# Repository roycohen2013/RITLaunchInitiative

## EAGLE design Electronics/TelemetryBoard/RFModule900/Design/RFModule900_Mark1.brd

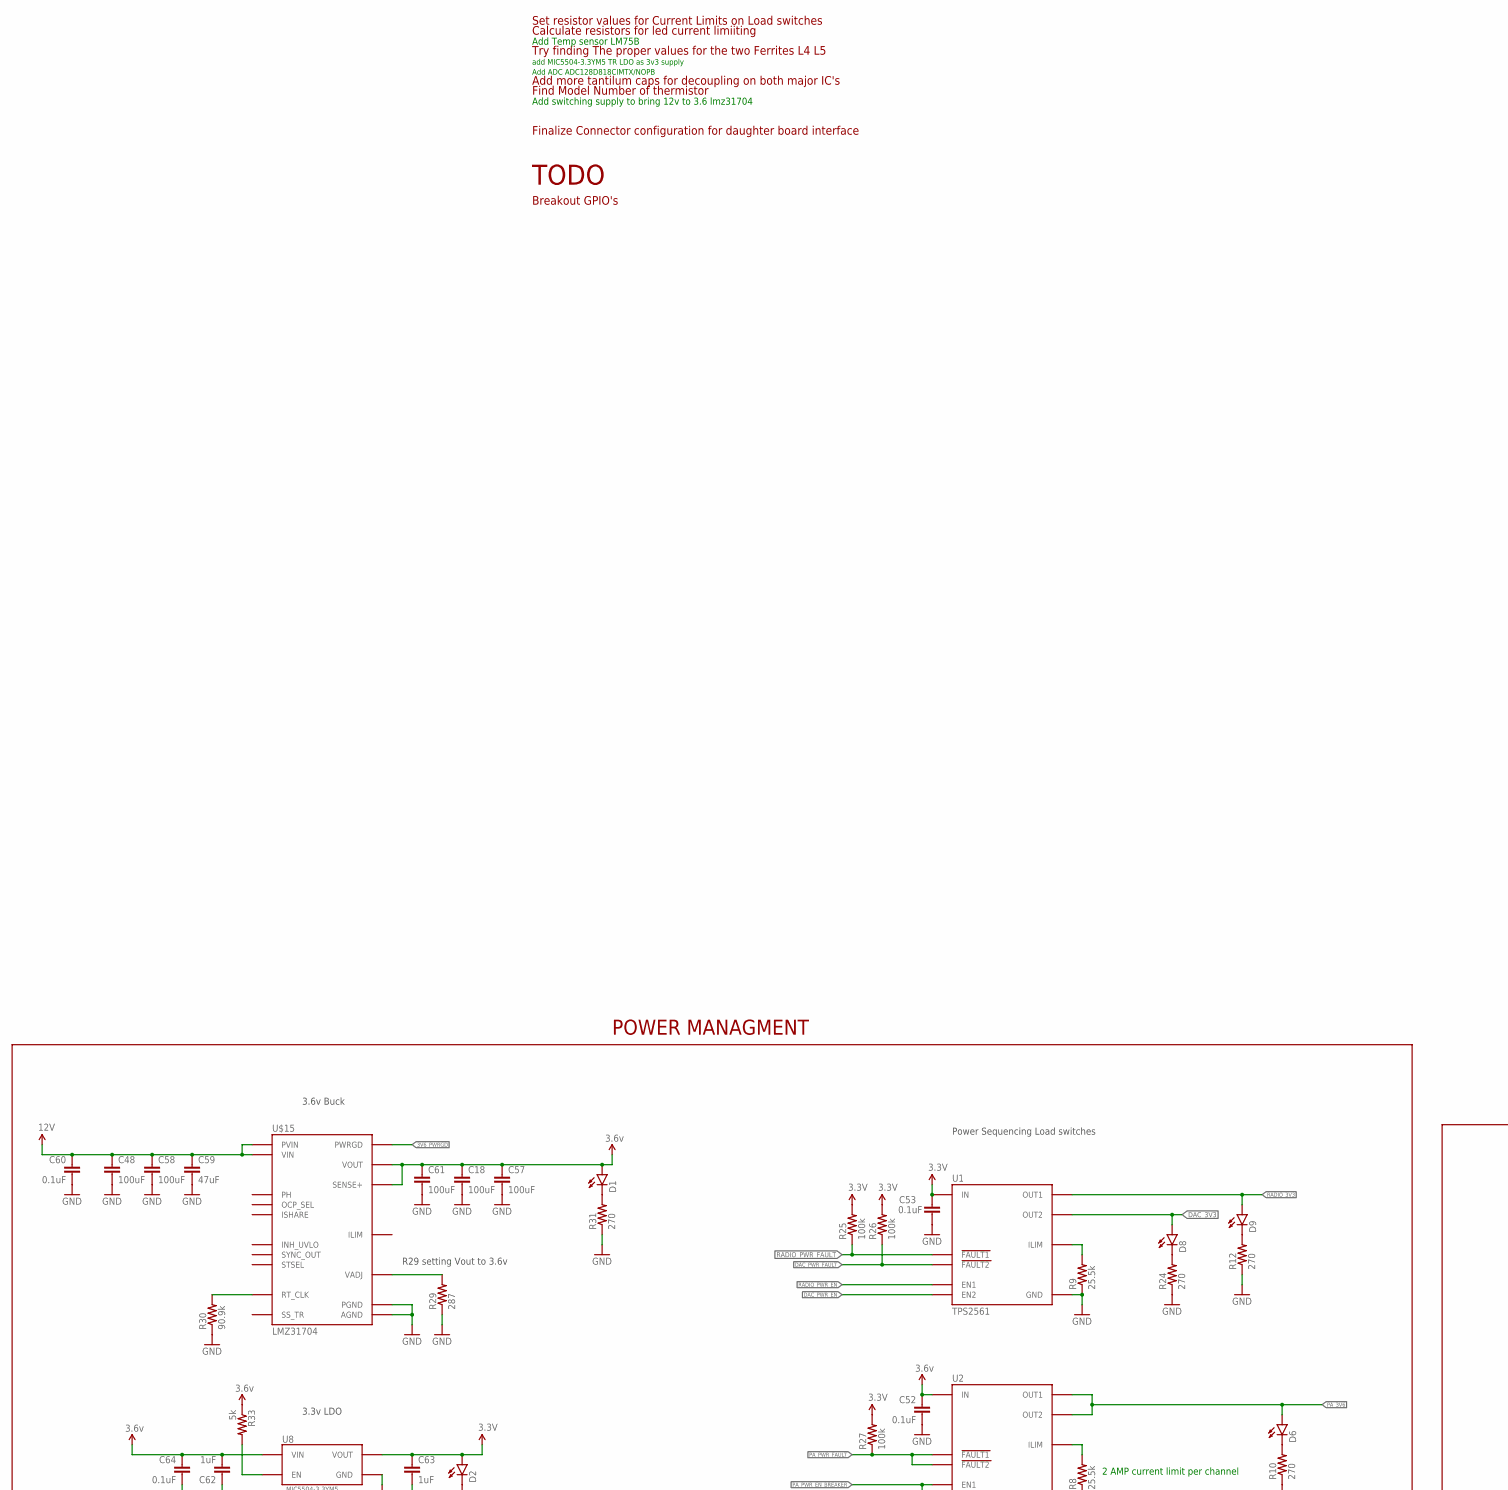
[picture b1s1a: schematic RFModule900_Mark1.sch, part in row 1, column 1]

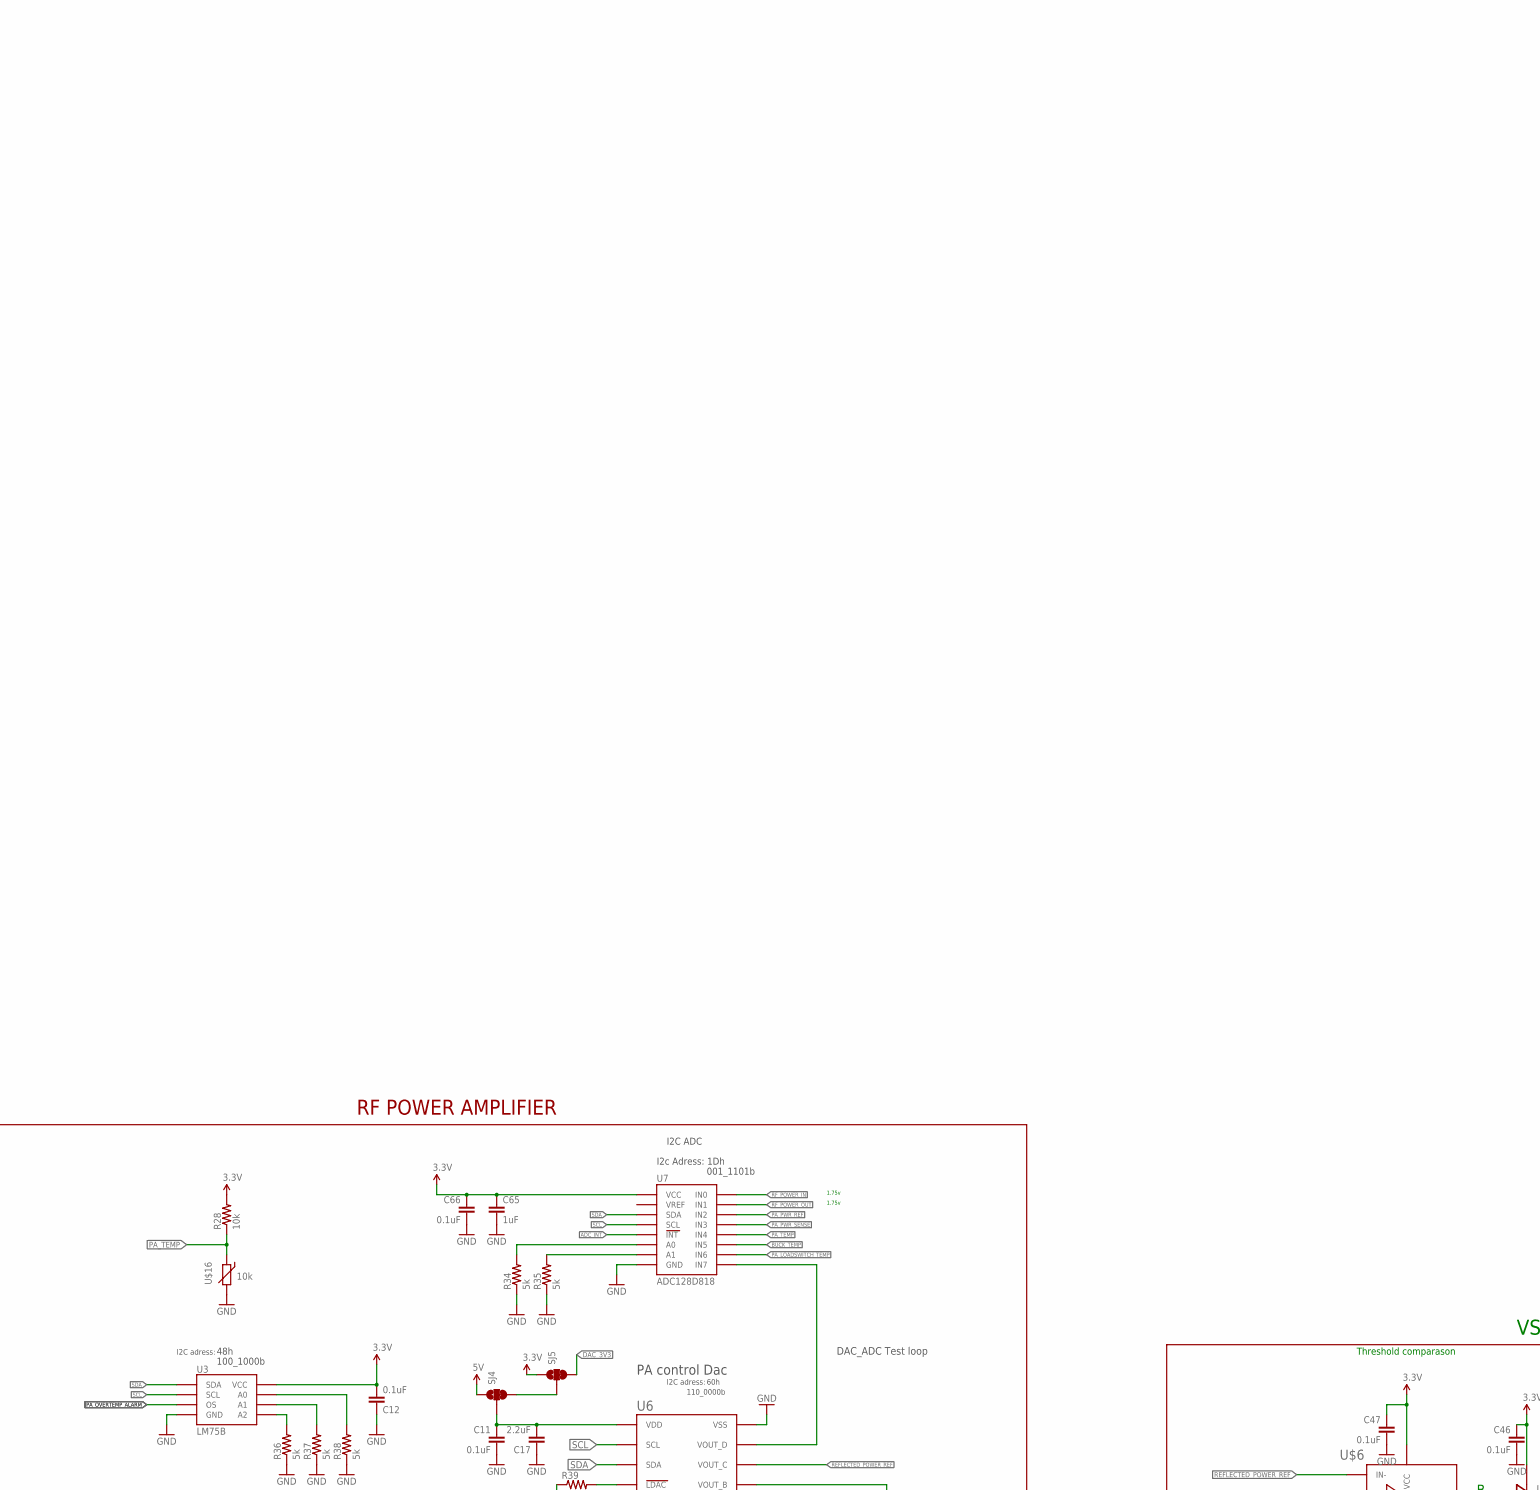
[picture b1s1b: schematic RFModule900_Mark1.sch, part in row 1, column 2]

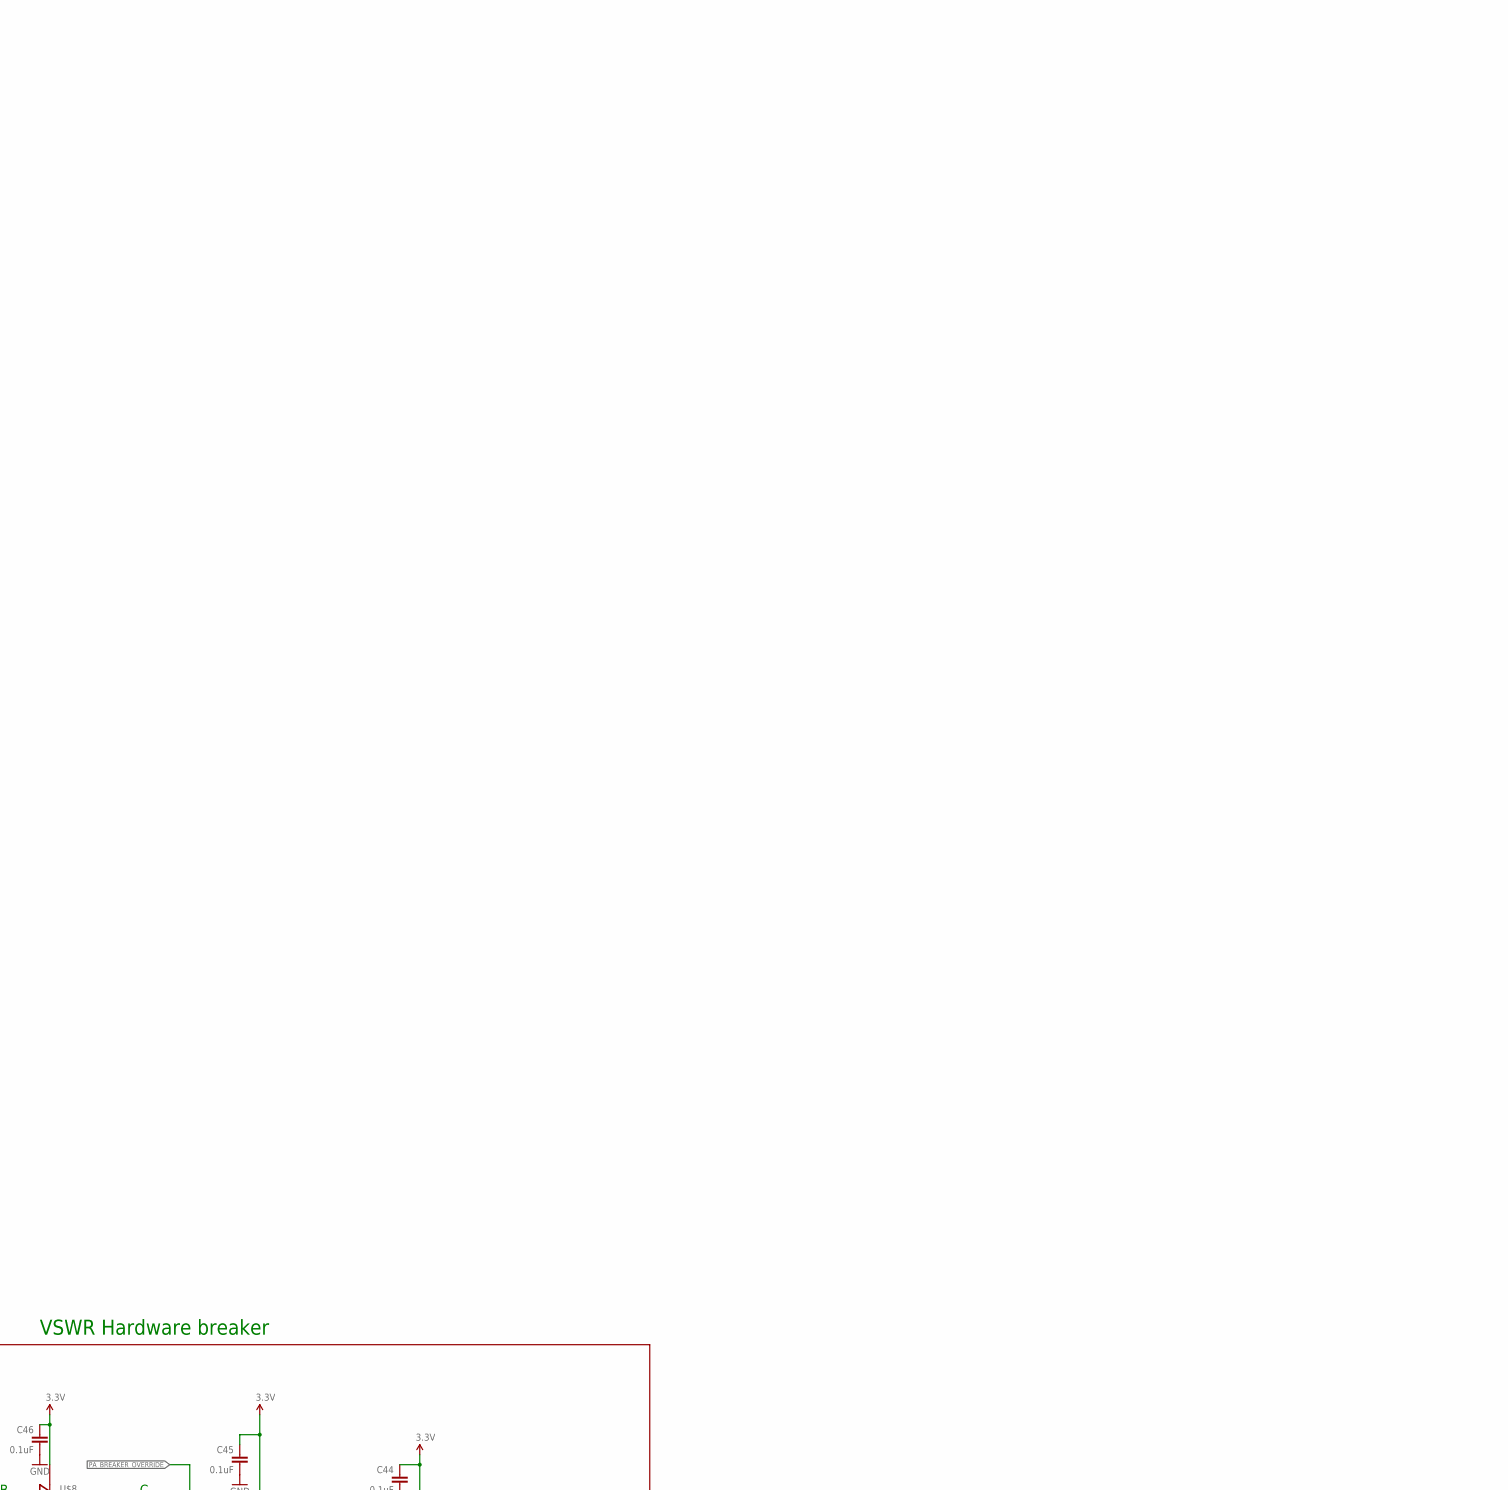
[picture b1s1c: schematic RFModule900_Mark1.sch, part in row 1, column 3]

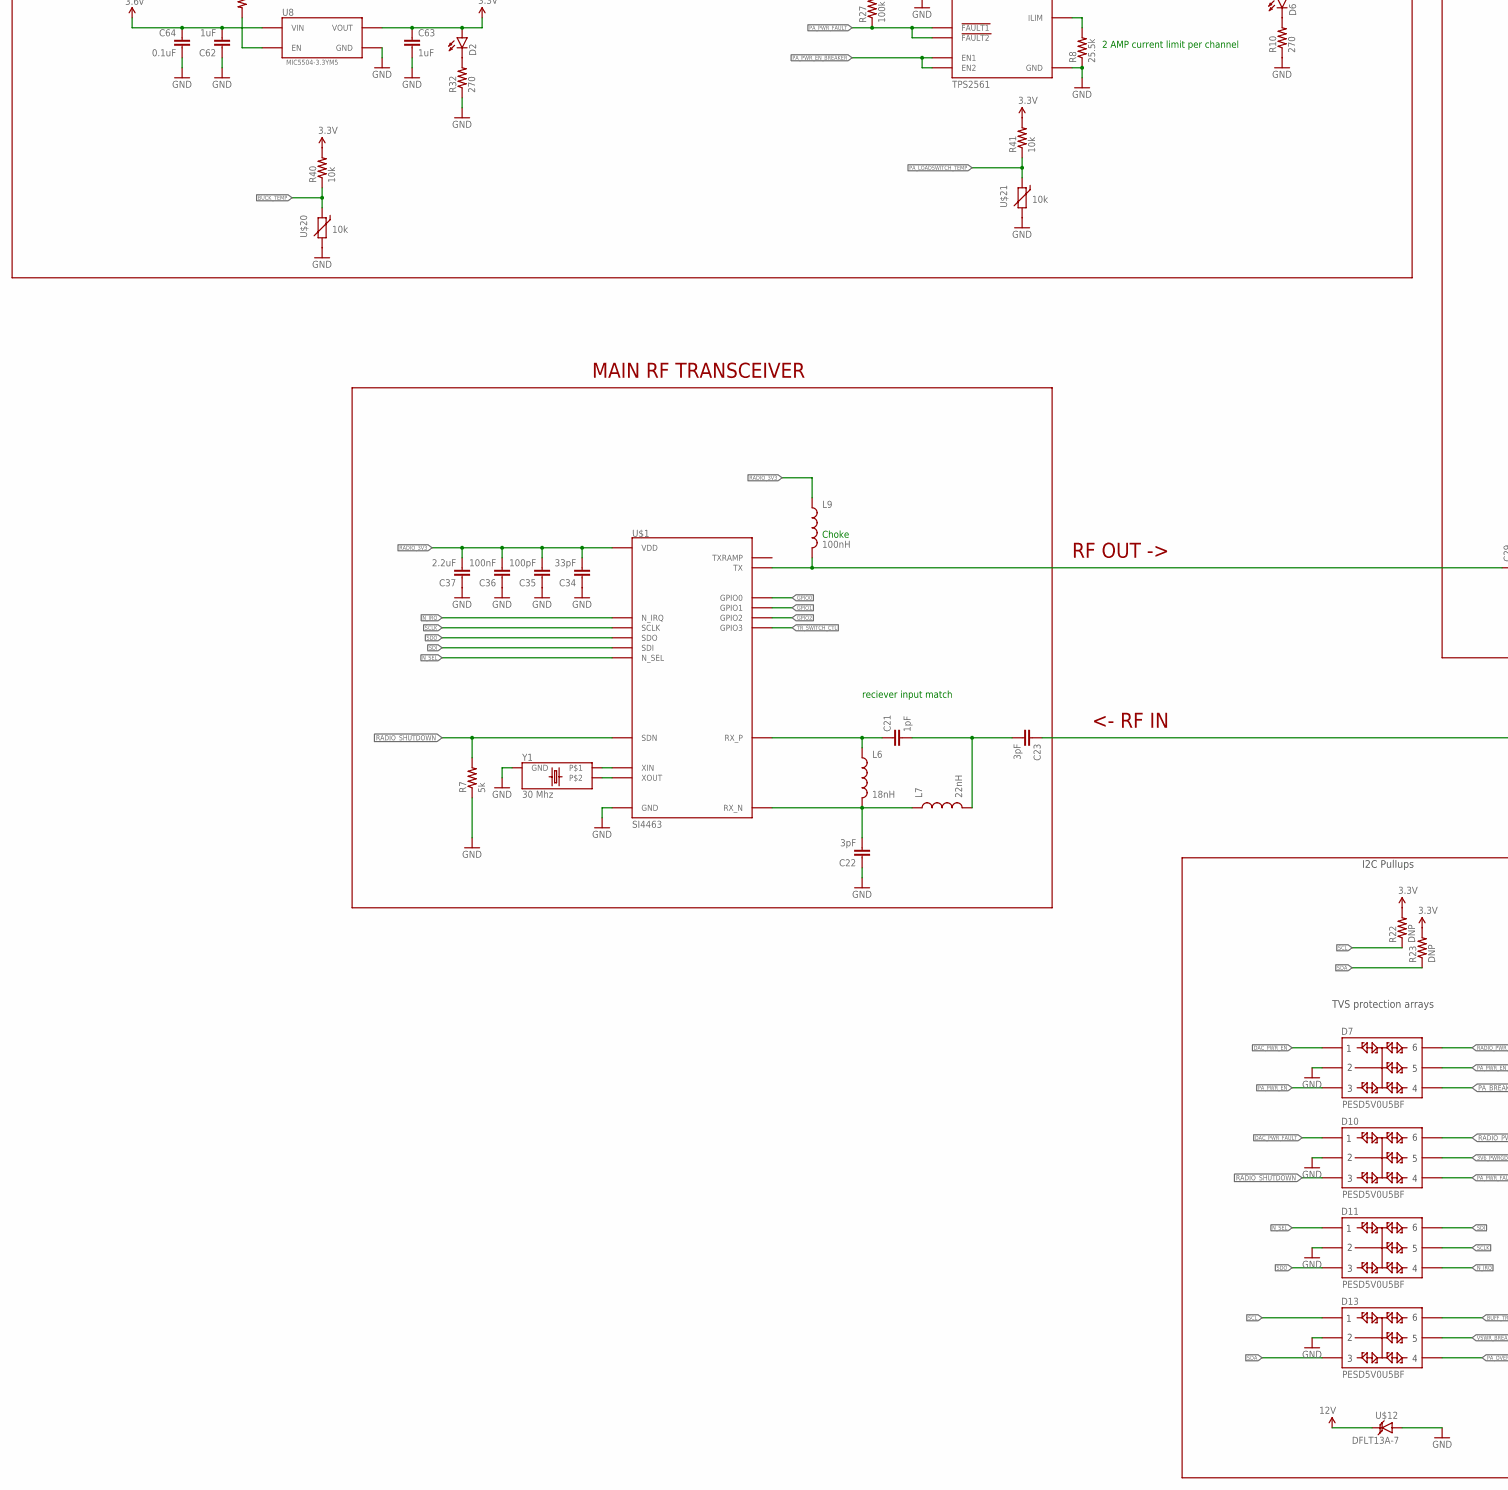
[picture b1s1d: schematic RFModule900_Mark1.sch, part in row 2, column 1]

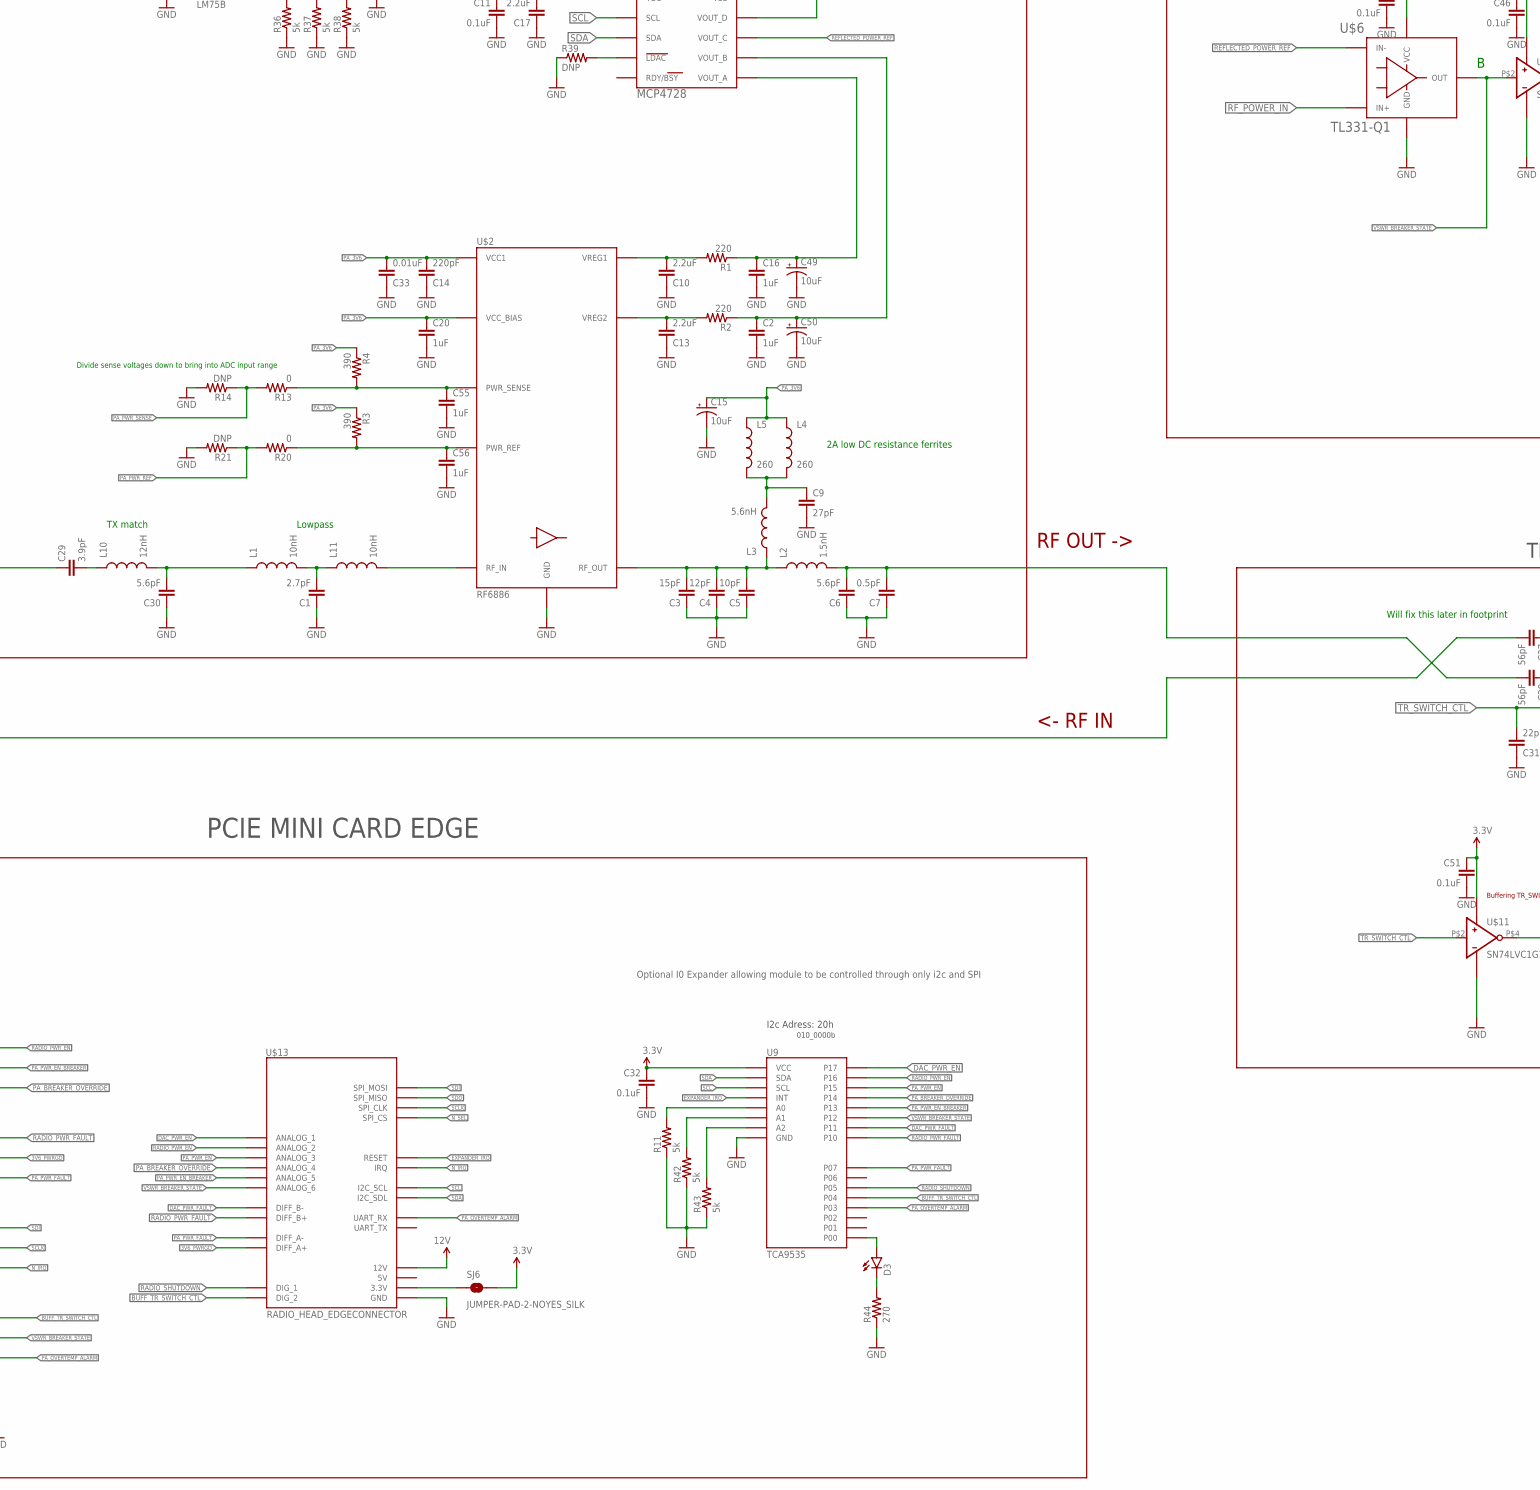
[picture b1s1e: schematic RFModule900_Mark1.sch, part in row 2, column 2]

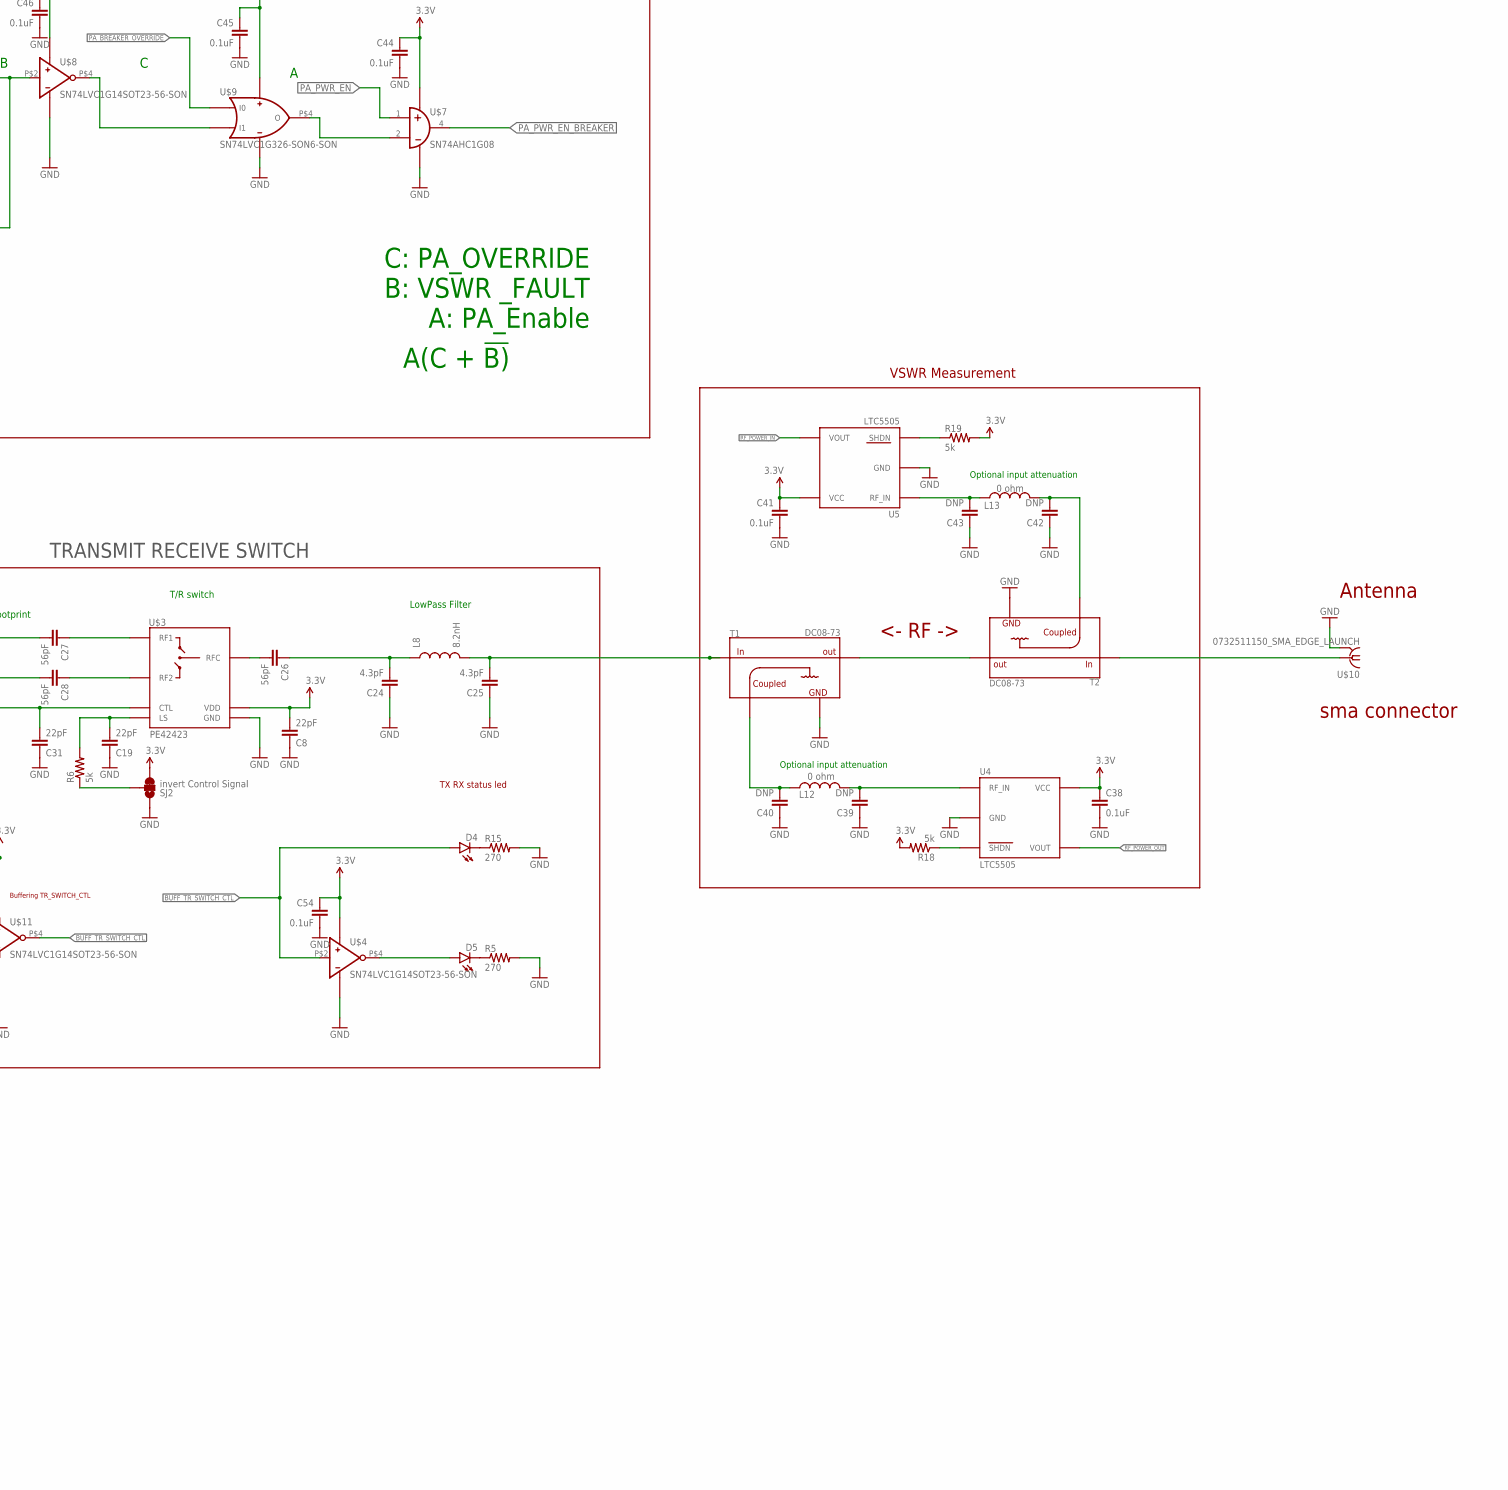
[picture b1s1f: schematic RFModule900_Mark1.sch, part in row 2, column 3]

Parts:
C1: 2.7pF; 0402-CAP
C2, C16: 1uF; 0402-CAP; MPN JMK105BJ225MVHF; DIGI 587-1453-1-ND
C3: 15pF; 0402-CAP; MPN 500R07S150JV4TD; DIGI 712-1261-1-ND
C4: 12pF; 0402-CAP; MPN 500R07S120JV4TD; DIGI 712-1257-1-ND
C5: 10pF; 0402-CAP; MPN 500R07S100JV4TD; DIGI 712-1253-1-ND
C6: 5.6pF; 0402-CAP; MPN 500R07S5R6BV4; MOUSER 609-500R07S5R6BV4T
C7: 0.5pF; 0402-CAP; MPN 500R07S0R5BV4TD; DIGI 712-1162-1-ND
C8, C19, C31: 22pF; 0402-CAP
C9: 27pF; 0402-CAP; DIGI 712-1277-1-ND
C10, C13, C17, C37: 2.2uF; 0402-CAP
C11, C12, C38, C41, C44, C45, C46, C47, C51, C52, C53, C54: 0.1uF; 0402-CAP
C14: 220pF; 0805; DIGI 712-1398-1-ND
C15, C49, C50: 10uF; EIA3216; MPN T491A105K016AT; DIGI 399-3678-1-ND
C18, C57, C61: 100uF; 1206; MPN GRM31CR60J107ME39K; DIGI 490-7217-2-ND
C20, C55, C56, C62, C63, C65: 1uF; 0402-CAP; MPN GRM155R61A105KE15D; DIGI 490-3890-1-ND
C21: 1pF; 0402-CAP
C22, C23: 3pF; 0402-CAP
C24, C25: 4.3pF; 0402-CAP
C26, C27, C28: 56pF; 0402-CAP
C29: 3.9pF; 0402-CAP
C30: 5.6pF; 0402-CAP
C32, C60, C64, C66: 0.1uF; 0402-CAP; MPN CC0402KRX7R7BB104; DIGI 311-1338-1-ND
C33: 0.01uF; 0402-CAP
C34: 33pF; 0402-CAP
C35: 100pF; 0402-CAP
C36: 100nF; 0402-CAP
C39, C40, C42, C43: DNP; 0402-CAP
C48, C58: 100uF; CERAMIC_CAP_1210
C59: 47uF; CERAMIC_CAP_1210
D1, D2, D3, D6, D8, D9: LED0603; LED-0603; DIGI 160-1447-1-ND
D4: LED0603; LED-0603; DIGI 160-1446-1-ND
D5: LED0603; LED-0603; DIGI 160-1647-1-ND
D7, D10, D11, D13: PESD5V0U5BF; 6-XFDFN
L1, L11: 10nH; C0402
L2: 1.5nH; 0603; MPN LL1608-FSL1N5S
L3: 5.6nH; C0402
L4, L5: 260; 0603; MPN BLM18EG221SN1D; DIGI 490-3992-1-ND
L6: 18nH; C0402
L7: 22nH; C0402
L8: 8.2nH; C0402
L9: 100nH; C0402
L10: 12nH; C0402
L12, L13: 0 ohm; C0402
R1, R2: 220; 0402-RES
R3, R4: 390; 0402-RES
R5, R10, R12, R15, R24, R31, R32, R44: 270; 0402-RES
R6, R7, R11, R18, R19, R33, R34, R35, R36, R37, R38, R42, R43: 5k; 0402-RES
R8, R9: 25.5k; 0402-RES
R13, R20: 0; 0402-RES
R14, R21, R22, R23, R39: DNP; 0402-RES
R25, R26, R27: 100k; 0402-RES
R28, R40, R41: 10k; 0402-RES
R29: 287; 0402-RES; MPN ERJ-2RKF2870X; DIGI P287LCT-ND
R30: 90.9k; 0402-RES
SJ2: invert Control Signal; PAD-JUMPER-3-2OF3_NC_BY_TRACE_YES_SILK_FULL_BOX
SJ4, SJ5: JUMPER-PAD-3-2OF3_NC_BY_TRACE_SMALL; PAD-JUMPER-3-2OF3_NC_BY_TRACE_YES_SILK_FULL_BOX
SJ6: JUMPER-PAD-2-NOYES_SILK; PAD-JUMPER-2-NO_YES_SILK
T1, T2: DC08-73; SOT23-6
U1, U2: TPS2561; 10-VFDFN
U3: LM75B; HWSON8
U4, U5: LTC5505; TSOT-23-5
U6: MCP4728; 10-MSOP
U7: ADC128D818; 16-TSSOP
U8: MIC5504-3.3YM5; SOT23-5
U9: TCA9535; 24-WQFN
U$1: SI4463; 20-VFQFN
U$2: RF6886; 24-VFQFN; DIGI 689-1091-1-ND
U$3: PE42423; 16-QFN
U$4, U$8, U$11: SN74LVC1G14SOT23-56-SON; 6-SON
U$6: TL331-Q1; SOT23-5
U$7: SN74AHC1G08; SOT23-5
U$9: SN74LVC1G326-SON6-SON; 6-SON
U$10: 0732511150_SMA_EDGE_LAUNCH; SMA_EDGE_LAUNCH
U$12: DFLT13A-7; POWERDI®123
U$13: RADIO_HEAD_EDGECONNECTOR; PCIE_MINI_CARDEDGE
U$15: LMZ31704; 42-QFN
U$16, U$20, U$21: 10k; 0402; MPN NCP15XH103F03RC; DIGI 490-4801-1-ND
Y1: 30 Mhz; 4-SMD_3.2_X_2.5; MPN 7M-30.000MEEQ-T; DIGI 887-1330-1-ND

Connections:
3.3V: C8.2, C12.2, C32.1, C38.1, C41.1, C44.1, C45.1, C46.1, C47.1, C51.1, C53.1, C54.1, C63.1, C65.1, C66.1, D2.A, R18.2, R19.2, R22.2, R23.2, R25.2, R26.2, R27.2, R28.2, R40.2, R41.2, SJ2.3, SJ5.1, SJ6.2, U1.P$2 (IN), U1.P$3 (IN), U3.P$8 (VCC), U4.P$5 (VCC), U5.P$5 (VCC), U7.5 (VCC), U8.5 (VOUT), U9.P$21 (VCC), U$3.P$16 (VDD), U$4.P$6 (VCC), U$6.5 (VCC), U$7.5 (VCC), U$8.P$6 (VCC), U$9.P$6 (VCC), U$11.P$6 (VCC)
3.6V: C18.1, C52.1, C57.1, C61.1, C62.2, C64.1, D1.A, R33.1, U2.P$2 (IN), U2.P$3 (IN), U8.1 (VIN), U$15.P$27 (SENSE+), U$15.P$34 (VOUT), U$15.P$35 (VOUT), U$15.P$36 (VOUT), U$15.P$37 (VOUT), U$15.P$38 (VOUT), U$15.P$41 (VOUT)
3V6_PWRGD: D10.P$5, U$13.P$18 (DIFF_A+), U$15.P$8 (PWRGD)
5V: SJ4.1
12V: C48.P$1 (1), C58.P$1 (1), C59.P$1 (1), C60.1, U$12.CATHODE, U$13.P$45 (12V), U$13.P$47 (12V), U$13.P$49 (12V), U$13.P$51 (12V), U$15.P$1 (PVIN), U$15.P$3 (VIN), U$15.P$11 (PVIN), U$15.P$12 (PVIN), U$15.P$39 (PVIN), U$15.P$40 (PVIN)
ADC_INT: U7.6 (INT)
BUCK_TEMP: R40.1, U7.11 (IN5), U$20.1
BUFF_TR_SWITCH_CTL: D4.A, D13.P$6, U9.P$5 (P04), U$4.P$2 (I), U$11.P$4 (O), U$13.P$25 (DIG_2)
DAC_3V3: D8.A, SJ5.3, U1.P$8 (OUT2)
DAC_PWR_EN: D7.P$1, U1.P$5 (EN2), U9.P$17 (P17), U$13.P$10 (ANALOG_1)
DAC_PWR_FAULT: D10.P$1, R26.1, U1.P$6 (FAULT2), U9.P$11 (P11), U$13.P$24 (DIFF_B-)
EXPANDER_IRQ: U9.P$22 (INT), U$13.P$9 (RESET)
GND: C1.1, C2.2, C3.1, C4.1, C5.1, C6.1, C7.1, C8.1, C9.2, C10.1, C11.2, C12.1, C13.1, C14.1, C15.C (-), C16.2, C17.1, C18.2, C19.1, C20.2, C22.1, C24.1, C25.1, C30.1, C31.1, C32.2, C33.1, C34.1, C35.1, C36.1, C37.1, C38.2, C39.1, C40.1, C41.2, C42.1, C43.1, C44.2, C45.2, C46.2, C47.2, C48.P$2 (2), C49.C (-), C50.C (-), C51.2, C52.2, C53.2, C54.2, C55.2, C56.2, C57.2, C58.P$2 (2), C59.P$2 (2), C60.2, C61.2, C62.1, C63.2, C64.2, C65.2, C66.2, D7.P$2, D10.P$2, D11.P$2, D13.P$2, R5.2, R7.1, R8.1, R9.1, R10.1, R11.1, R12.1, R14.2, R15.2, R21.2, R24.1, R29.1, R30.1, R31.1, R32.1, R34.1, R35.1, R36.1, R37.1, R38.1, R39.1, R42.1, R43.1, R44.1, SJ2.1, T1.1 (GND), T1.2 (GND), T1.5 (GND), T2.1 (GND), T2.2 (GND), T2.5 (GND), U1.GNDPAD (GND), U1.P$1 (GND), U2.GNDPAD (GND), U2.P$1 (GND), U3.P$4 (GND), U4.P$2 (GND), U5.P$2 (GND), U6.P$10 (VSS), U7.4 (GND), U8.2 (GND), U9.GND_PAD (GND), U9.P$9 (GND), U$1.GND_PAD (GND), U$1.P$18 (GND), U$2.P$GND_PAD (GND), U$3.P$1 (GND), U$3.P$3 (GND), U$3.P$4 (GND), U$3.P$5 (GND), U$3.P$6 (GND), U$3.P$8 (GND), U$3.P$9 (GND), U$3.P$10 (GND), U$3.P$12 (GND), U$3.P$13 (GND), U$3.P$GNDPAD (GND), U$4.P$3 (GND), U$6.2 (GND), U$7.3 (GND), U$8.P$3 (GND), U$9.P$3 (GND), U$10.GND@1 (GND), U$10.GND@2 (GND), U$10.GND@3 (GND), U$10.GND@5 (GND), U$11.P$3 (GND), U$12.ANODE, U$13.P$3 (GND), U$13.P$4 (GND), U$13.P$7 (GND), U$13.P$8 (GND), U$13.P$11 (GND), U$13.P$12 (GND), U$13.P$15 (GND), U$13.P$16 (GND), U$13.P$22 (GND), U$13.P$27 (GND), U$13.P$28 (GND), U$13.P$30 (GND), U$13.P$34 (GND), U$13.P$38 (GND), U$13.P$42 (GND), U$13.P$44 (GND), U$13.P$46 (GND), U$13.P$48 (GND), U$15.P$2 (AGND), U$15.P$20 (PGND), U$15.P$21 (PGND), U$15.P$23 (AGND), U$15.P$31 (PGND), U$15.P$32 (PGND), U$15.P$33 (PGND), U$16.2, U$20.2, U$21.2, Y1.P$2 (GND), Y1.P$4 (GND)
GPIO0: U$1.P$9 (GPIO0)
GPIO1: U$1.P$10 (GPIO1)
GPIO2: U$1.P$19 (GPIO2)
unnamed: C1.2, L1.2, L11.1
unnamed: C10.2, R1.2, U$2.P$19 (VREG1)
unnamed: U$8.P$4 (O), U$9.P$2 (I1)
unnamed: D3.C, R44.2
unnamed: C6.2, C7.2, C28.2, L2.2
unnamed: C9.1, L3.2, L4.2, L5.2
unnamed: SJ6.1, U$13.P$29 (3.3V), U$13.P$31 (3.3V), U$13.P$33 (3.3V), U$13.P$35 (3.3V), U$13.P$37 (3.3V), U$13.P$39 (3.3V)
unnamed: C3.2, C4.2, C5.2, L2.1, L3.1, U$2.P$13 (RF_OUT), U$2.P$14 (RF_OUT), U$2.P$15 (RF_OUT), U$2.P$16 (RF_OUT), U$2.P$17 (RF_OUT), U$2.P$18 (RF_OUT)
unnamed: C13.2, R2.2, U$2.P$5 (VREG2)
unnamed: C24.2, C26.1, L8.1
unnamed: R9.2, U1.P$7 (ILIM)
unnamed: C21.1, L6.1, U$1.P$2 (RX_P)
unnamed: C21.2, C23.2, L7.2
unnamed: C23.1, C27.2
unnamed: C25.2, L8.2, T1.4 (IN)
unnamed: C26.2, U$3.P$7 (RFC)
unnamed: L11.2, U$2.P$6 (RF_IN)
unnamed: U6.P$9 (VOUT_D), U7.9 (IN7)
unnamed: U$7.2 (I1), U$9.P$4 (O)
unnamed: C29.1, L9.2, U$1.P$4 (TX)
unnamed: C29.2, L10.1
unnamed: C30.2, L1.1, L10.2
unnamed: C27.1, U$3.P$2 (RF1)
unnamed: C28.1, U$3.P$11 (RF2)
unnamed: R6.1, SJ2.2
unnamed: C19.2, R6.2, U$3.P$15 (LS)
unnamed: C22.2, L6.2, L7.1, U$1.P$3 (RX_N)
unnamed: U$1.P$17 (XIN), Y1.P$1
unnamed: U$1.P$16 (XOUT), Y1.P$3
unnamed: D6.C, R10.2
unnamed: D8.C, R24.2
unnamed: R8.2, U2.P$7 (ILIM)
unnamed: D5.C, R5.1
unnamed: D5.A, U$4.P$4 (O)
unnamed: D4.C, R15.1
unnamed: R18.1, U4.P$3 (SHDN)
unnamed: C40.2, L12.1, T1.3 (COUPLED)
unnamed: C39.2, L12.2, U4.P$1 (RF_IN)
unnamed: T1.6 (OUT), T2.6 (OUT)
unnamed: R19.1, U5.P$3 (SHDN)
unnamed: C43.2, L13.1, U5.P$1 (RF_IN)
unnamed: C42.2, L13.2, T2.3 (COUPLED)
unnamed: T2.4 (IN), U$10.P (1)
unnamed: C55.1, R4.2, R13.1, U$2.P$23 (PWR_SENSE)
unnamed: C56.1, R3.2, R20.1, U$2.P$24 (PWR_REF)
unnamed: C11.1, C17.2, SJ4.2, U6.P$1 (VDD)
unnamed: D9.C, R12.2
unnamed: SJ4.3, SJ5.2
unnamed: R29.2, U$15.P$26 (VADJ)
unnamed: R30.2, U$15.P$22 (RT_CLK)
unnamed: D2.C, R32.2
unnamed: R33.2, U8.3 (EN)
unnamed: D1.C, R31.2
unnamed: R35.2, U7.8 (A1)
unnamed: R34.2, U7.7 (A0)
unnamed: R36.2, U3.P$5 (A2)
unnamed: R37.2, U3.P$6 (A1)
unnamed: R38.2, U3.P$7 (A0)
unnamed: R39.2, U6.P$4 (LDAC)
unnamed: D3.A, U9.P$1 (P00)
unnamed: R11.2, U9.P$18 (A0)
unnamed: R42.2, U9.P$23 (A1)
unnamed: R43.2, U9.P$24 (A2)
N_IRQ: D11.P$4, U$1.P$11 (N_IRQ), U$13.P$32 (IRQ)
N_SEL: D11.P$1, U$1.P$15 (N_SEL), U$13.P$6 (SPI_CS)
PA_3V6: C14.2, C15.A (+), C20.1, C33.2, D6.A, L4.1, L5.1, R3.1, R4.1, U2.P$8 (OUT2), U2.P$9 (OUT1), U$2.P$1 (VCC1), U$2.P$2 (VCC1), U$2.P$3 (VCC1), U$2.P$22 (VCC_BIAS)
PA_BREAKER_OVERRIDE: D7.P$4, U9.P$14 (P14), U$9.P$1 (I0), U$13.P$17 (ANALOG_4)
PA_LOADSWITCH_TEMP: R41.1, U7.10 (IN6), U$21.1
PA_OVERTEMP_ALARM: D13.P$4, U3.P$3 (OS), U9.P$4 (P03), U$13.P$52 (UART_RX)
PA_PWR_EN: D7.P$3, U9.P$15 (P15), U$7.1 (I0), U$13.P$14 (ANALOG_3)
PA_PWR_EN_BREAKER: D7.P$5, U2.P$4 (EN1), U2.P$5 (EN2), U9.P$13 (P13), U$7.4 (O), U$13.P$19 (ANALOG_5)
PA_PWR_FAULT: D10.P$4, R27.1, U2.P$6 (FAULT2), U2.P$10 (FAULT1), U9.P$8 (P07), U$13.P$20 (DIFF_A-)
PA_PWR_REF: R20.2, R21.1, U7.14 (IN2)
PA_PWR_SENSE: R13.2, R14.1, U7.13 (IN3)
PA_TEMP: R28.1, U7.12 (IN4), U$16.1
RADIO_3V3: C34.2, C35.2, C36.2, C37.2, D9.A, L9.1, U1.P$9 (OUT1), U$1.P$6 (VDD), U$1.P$8 (VDD)
RADIO_PWR_EN: D7.P$6, U1.P$4 (EN1), U9.P$16 (P16), U$13.P$13 (ANALOG_2)
RADIO_PWR_FAULT: D10.P$6, R25.1, U1.P$10 (FAULT1), U9.P$10 (P10), U$13.P$26 (DIFF_B+)
RADIO_SHUTDOWN: D10.P$3, R7.2, U9.P$6 (P05), U$1.P$1 (SDN), U$13.P$23 (DIG_1)
REFLECTED_POWER_REF: U6.P$8 (VOUT_C), U$6.1 (IN-)
RF_POWER_IN: U5.P$4 (VOUT), U7.16 (IN0), U$6.3 (IN+)
RF_POWER_OUT: U4.P$4 (VOUT), U7.15 (IN1)
SCL: D13.P$1, R22.1, U3.P$2 (SCL), U6.P$2 (SCL), U7.3 (SCL), U9.P$19 (SCL), U$13.P$40 (I2C_SCL)
SCLK: D11.P$5, U$1.P$12 (SCLK), U$13.P$2 (SPI_CLK)
SDA: D13.P$3, R23.1, U3.P$1 (SDA), U6.P$3 (SDA), U7.2 (SDA), U9.P$20 (SDA), U$13.P$36 (I2C_SDL)
SDI: D11.P$6, U$1.P$14 (SDI), U$13.P$1 (SPI_MOSI)
SDO: D11.P$3, U$1.P$13 (SDO), U$13.P$5 (SPI_MISO)
TR_SWITCH_CTL: C31.2, U$1.P$20 (GPIO3), U$3.P$14 (CTL), U$11.P$2 (I)
VREG1_DAC: C16.1, C49.A (+), R1.1, U6.P$6 (VOUT_A)
VREG2_DAC: C2.1, C50.A (+), R2.1, U6.P$7 (VOUT_B)
VSWR_BREAKER_STATE: D13.P$5, U9.P$12 (P12), U$6.4 (OUT), U$8.P$2 (I), U$13.P$21 (ANALOG_6)

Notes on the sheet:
2A low DC resistance ferrites
LowPass Filter
reciever input match
Choke
TX match
Lowpass
T/R switch
RF POWER AMPLIFIER
MAIN RF TRANSCEIVER
POWER MANAGMENT
TRANSMIT RECEIVE SWITCH
RF OUT ->
<- RF IN
<- RF ->
Antenna
sma connector
TX RX status led
TODO
Set resistor values for Current Limits on Load switches
Calculate resistors for led current limiiting
Add more tantilum caps for decoupling on both major IC's
Find Model Number of thermistor
Finalize Connector configuration for daughter board interface
Breakout GPIO's
Try finding The proper values for the two Ferrites L4 L5
A(C + !B)
A: PA_Enable
C: PA_OVERRIDE
B: VSWR _FAULT
Will fix this later in footprint
VSWR Hardware breaker
Threshold comparason
Add Temp sensor LM75B
Optional input attenuation
VSWR Measurement
Buffering TR_SWITCH_CTL
2 AMP current limit per channel
Divide sense voltages down to bring into ADC input range
Add ADC ADC128D818CIMTX/NOPB
add MIC5504-3.3YM5 TR LDO as 3v3 supply

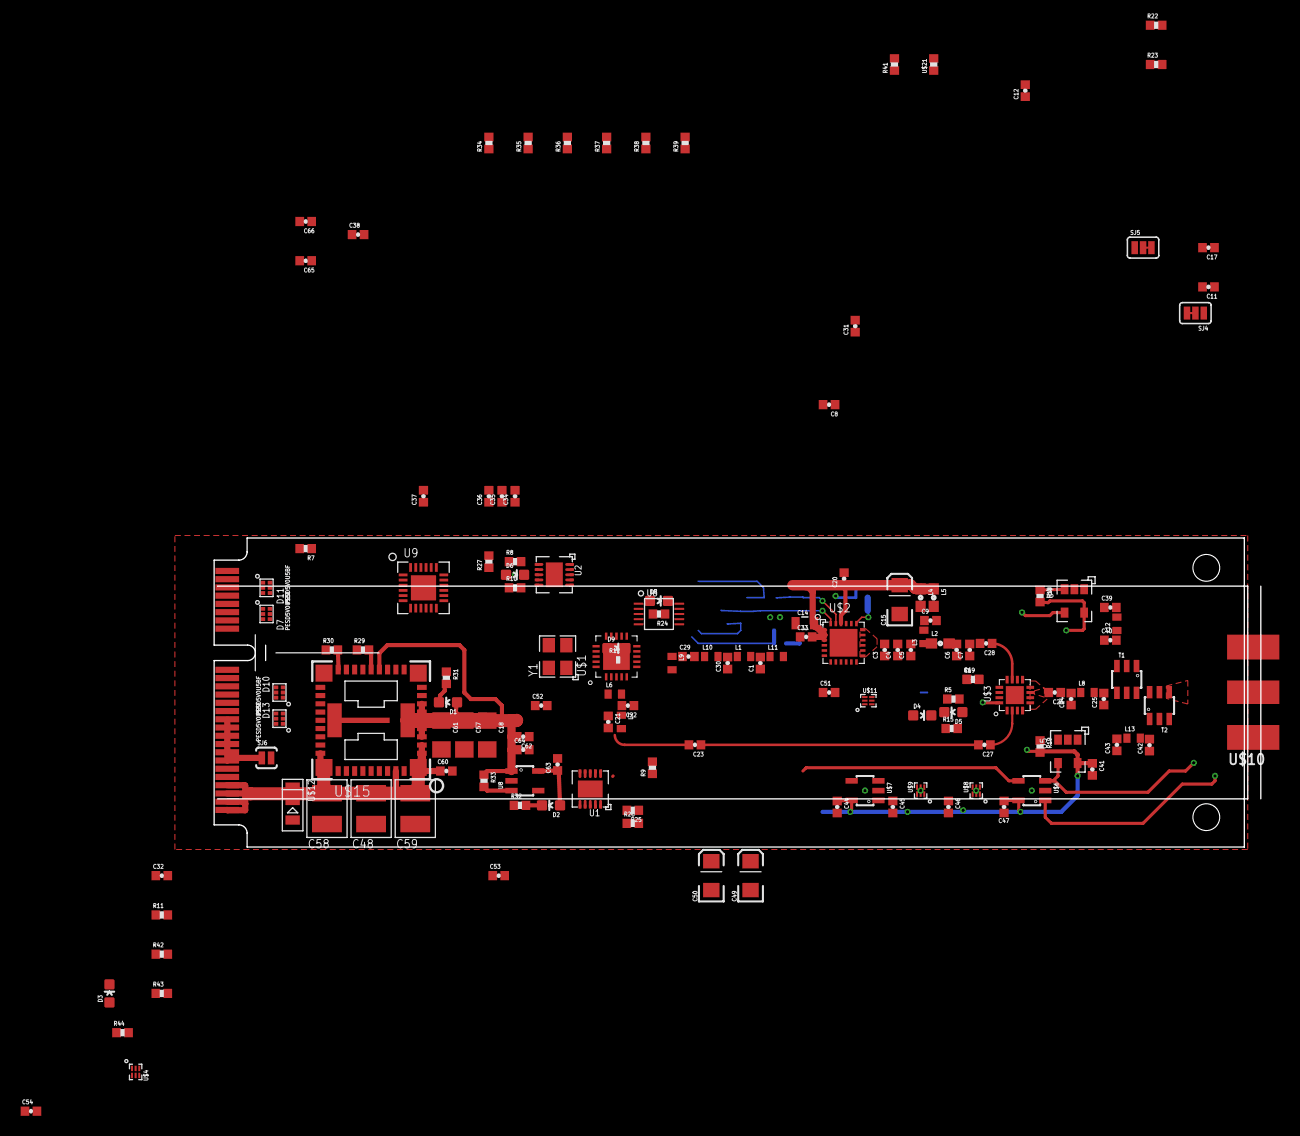
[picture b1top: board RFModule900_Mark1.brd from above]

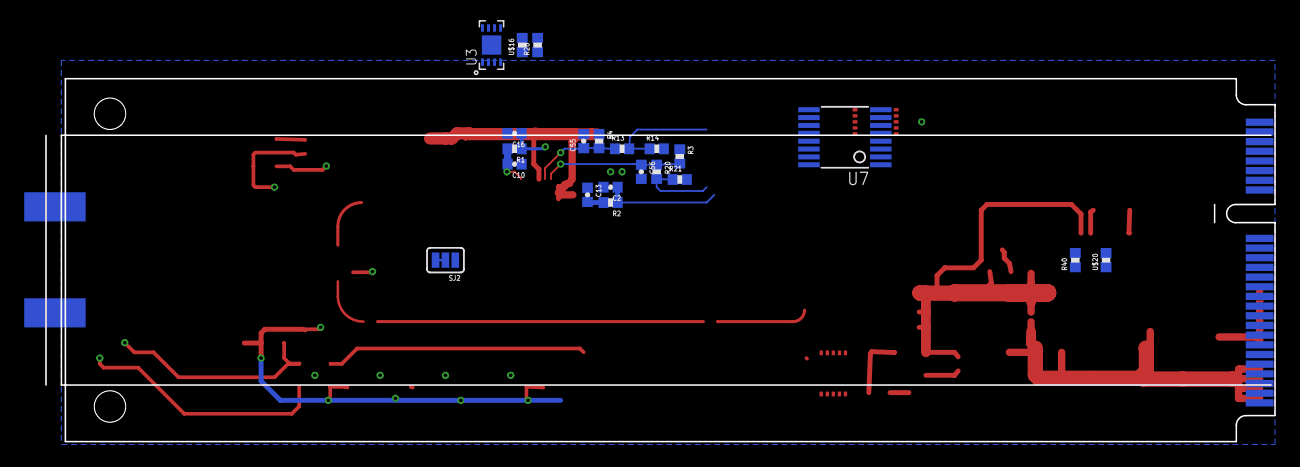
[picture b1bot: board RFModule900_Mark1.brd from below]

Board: 4 copper layers, 101.6 x 30.0 mm, 166 parts (21 on the bottom side), 102 nets.

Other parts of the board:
U$5: PCIE_36_CARDEDGE

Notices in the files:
parts and their libraries:
SparkFun-Capacitors: Licensing: Creative Commons ShareAlike 4.0 International - https://creativecommons.org/licenses/by-sa/4.0
SparkFun-Aesthetics: Released under the Creative Commons
SparkFun-Aesthetics: https://creativecommons.org/licenses/by-sa/4.0
